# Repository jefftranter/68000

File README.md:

# 68000 single-board retro-computing project
Designs and code related to the Motorola 68000 microprocessor.

## Building the project hardware
1. [Order the board](TS2/v2.1/README.md)
2. Order the parts from the [bill of materials (BOM)](TS2/v2.1/bom.pdf)
3. Order the two FT232 USB -> serial breakout boards
4. Order the chip sockets:

| Layout    | Qty   | Width (inches)    | Notes                                 |
|:---       | ---:  | ---:              |:---                                   |
| DIP-8     | 1     | 0.3               | For the 555                           |
| DIP-14    | 17    | 0.3               | For a lot                             |
| DIP-16    | 8     | 0.3               | For even more                         |
| DIP-24    | 2     | 0.6               | Double width: for serial interface    |
| DIP-28    | 8     | 0.6               | Double width: for RAM & ROM           |
| DIP-64    | 1     | 0.9               | Triple width: for CPU.                |

The DIP-64 can be a little hard to obtain, you could cut DIP-40 sockets to same effect. However, it's inadvisable to 
directly solder the CPU directly to the board. If the heat damages the chip, there's 64 pins to de-solder.

5. Solder in the sockets. Applying some soldering flux can be of great help: the IC soldering pads are tiny, mainly to 
save space on the board.
6. Solder in the rest of the components
7. [Flash the ROM chips](http://jefftranter.blogspot.com/2016/12/building-68000-single-board-computer_7.html)
8. Fit all ICs into their sockets
9. Connect power (preferably through a lab bench power supply)
10. Connect a PC to the board through USB
11. Watch it boot
12. Have some retro-computing fun!

Copyright (c) 2016-2023 by Jeff Tranter <tranter@pobox.com>

The hardware design is Open Source Hardware, licensed under the The TAPR
Open Hardware License. You are welcome to build the circuit and use my
PCB layout.
See https://web.tapr.org/OHL/TAPR_Open_Hardware_License_v1.0.txt

Some code here is entirely written by me and others are ports of
existing software. Software written by me is released under the
following license:

Licensed under the Apache License, Version 2.0 (the "License");
you may not use this file except in compliance with the License.
You may obtain a copy of the License at

  http://www.apache.org/licenses/LICENSE-2.0

Unless required by applicable law or agreed to in writing, software
distributed under the License is distributed on an "AS IS" BASIS,
WITHOUT WARRANTIES OR CONDITIONS OF ANY KIND, either express or implied.
See the License for the specific language governing permissions and
limitations under the License.

Documentation written by me is licensed under a Creative Commons
Attribution 4.0 International License.
See https://creativecommons.org/licenses/by/4.0/

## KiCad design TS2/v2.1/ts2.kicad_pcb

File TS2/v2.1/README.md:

# TS2 PCB project

This is a Kicad project for the Teesside TS2 single board computer
from the book "Microprocessor Systems Design - 68000 Hardware,
Software, and Interfacing", third edition, by Alan Clements.

This is a modified version that simplifies the design by removing
circuitry that is not needed for operation as a single board computer.
Specifically, removed was:

- backplane interface and associated buffering.

- interrupt priority encoding and acknowledge circuitry.

- line drivers and receivers for serial ports (FTDI USB to serial
  adaptors are used instead) and support for host/terminal transparent
  mode. This also removes the need for +12V/-12V power supplies.

This is version 2.1 that makes the following additional changes:

- The hard to obtain 25LS2548 chip is replaced by more commonly
  available parts.

- The hard to obtain MC14411 baud rate generator is replaced by a
  smaller, simpler circuit using the more easily obtained 74HC4060.

See more details on my blog at http://jefftranter.blogspot.ca/

## PCB printing
For your convenience, a [v2.1-gerbers.zip](v2.1-gerbers.zip) zip file is included here that you can directly feed to a printing facility. It includes the gerber files for the copper tracings, soldermasks, silk screens, drill file and other printing requirements. 

The individual gerber files are included (duplicated) as well in this directory for direct inspection in KiCad. Don't forget to update the files in the zip if you export using different settings.

The files were generated with KiCad v5.1.4 using the following settings. Note that your PCB manufacturer may require other settings. Check their site for the proper gerber and drill file export settings - don't use a printing facility that doesn't specify how to export the files!

### Gerber export settings

### Drill file export

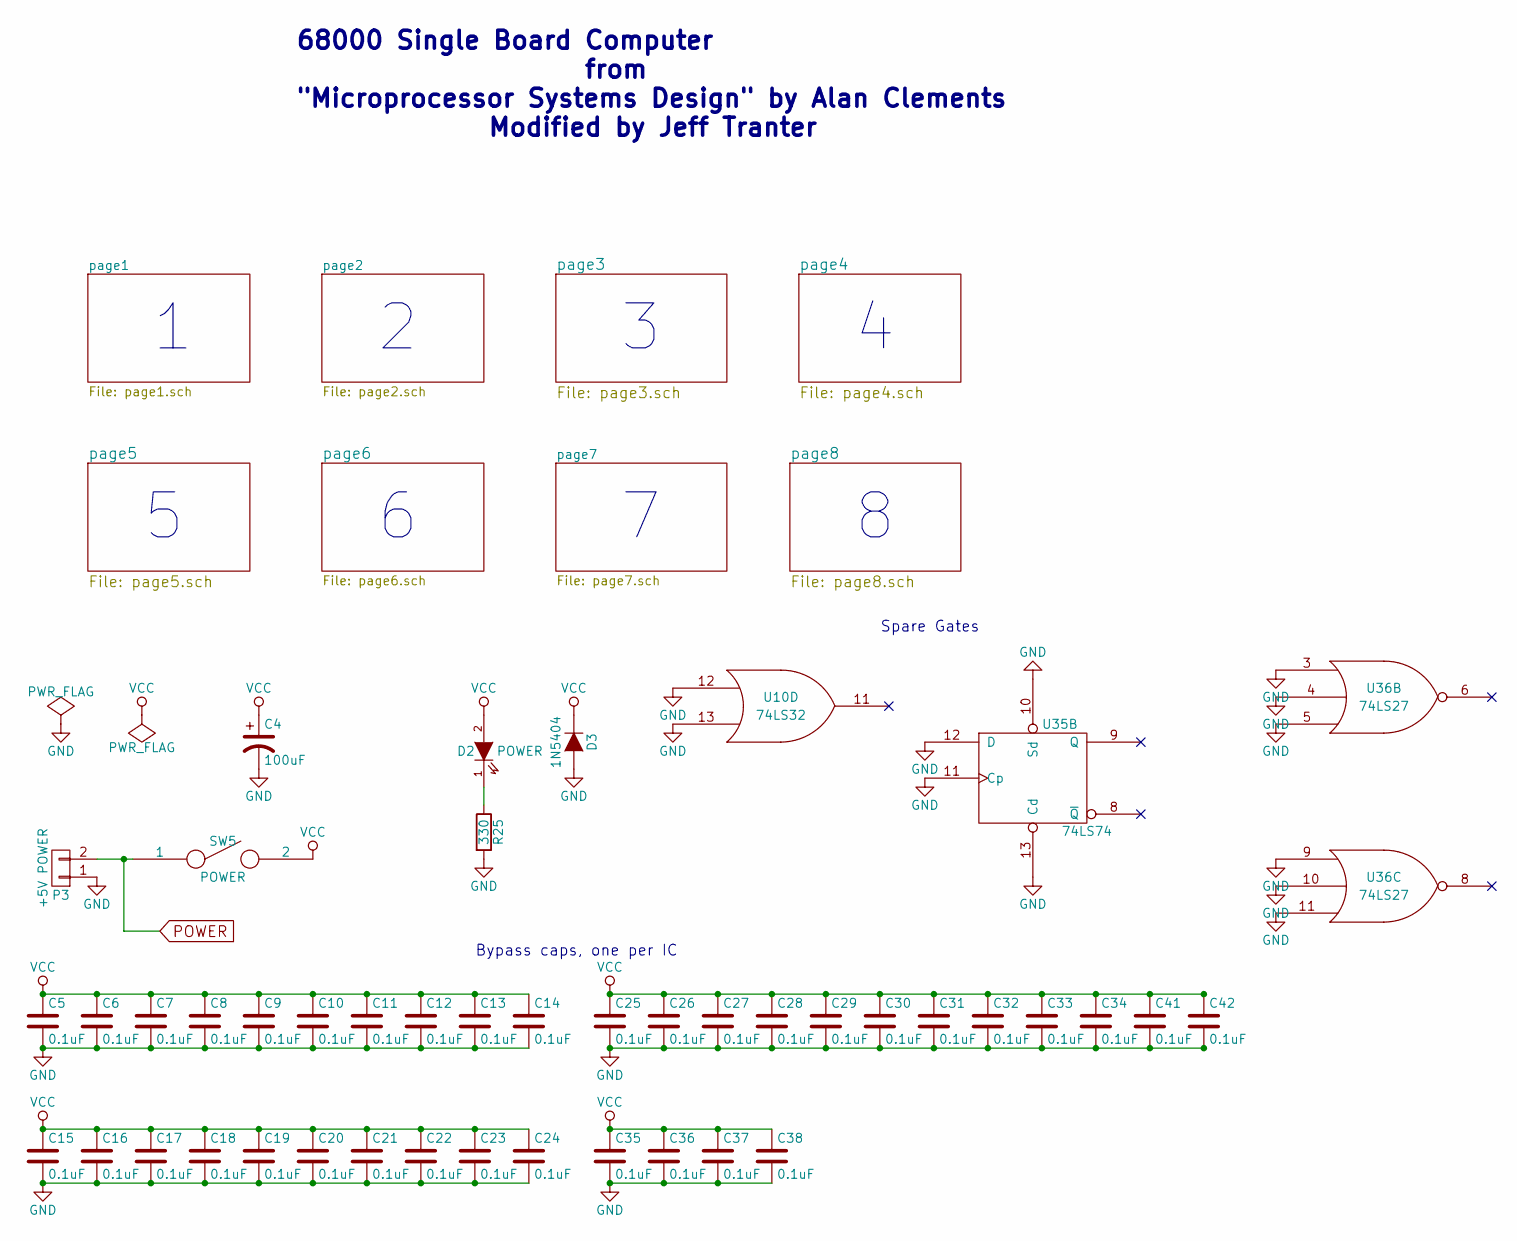
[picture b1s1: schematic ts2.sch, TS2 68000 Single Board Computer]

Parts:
C4: 100uF; C_Radial_D5_L6_P2.5
C5, C6, C7, C8, C9, C10, C11, C12, C13, C14, C15, C16, C17, C18, C19, C20, C21, C22, C23, C24, C25, C26, C27, C28, C29, C30, C31, C32, C33, C34, C35, C36, C37, C38, C41, C42: 0.1uF; C_Disc_D3_P2.5
D2: POWER; PINHEAD1-2
D3: 1N5404; Diode_DO-35_SOD27_Horizontal_RM10
P3: +5V POWER; PINHEAD1-2
R25: 330; Resistor_Horizontal_RM7mm
SW5: POWER; PINHEAD1-3
U10: 74LS32; DIP-14_W7.62mm
U35: 74LS74; DIP-14_W7.62mm
U36: 74LS27; DIP-14_W7.62mm

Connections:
GND: C4.2, C5.2, C6.2, C7.2, C8.2, C9.2, C10.2, C11.2, C12.2, C13.2, C14.2, C15.2, C16.2, C17.2, C18.2, C19.2, C20.2, C21.2, C22.2, C23.2, C24.2, C25.2, C26.2, C27.2, C28.2, C29.2, C30.2, C31.2, C32.2, C33.2, C34.2, C35.2, C36.2, C37.2, C38.2, C41.2, C42.2, D3.2 (A), P3.1, R25.2, U10.7 (GND), U10.12, U10.13, U35.7 (GND), U35.10 (Sd), U35.11 (Cp), U35.12 (D), U35.13 (Cd), U36.3, U36.4, U36.5, U36.7 (GND), U36.9, U36.10, U36.11; also elsewhere on the board
unnamed: D2.1 (K), R25.1
POWER: P3.2, SW5.1; also elsewhere on the board

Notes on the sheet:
68000 Single Board Computer from "Microprocessor Systems Design" by Alan Clements Modified by Jeff Tranter
Bypass caps, one per IC
Spare Gates

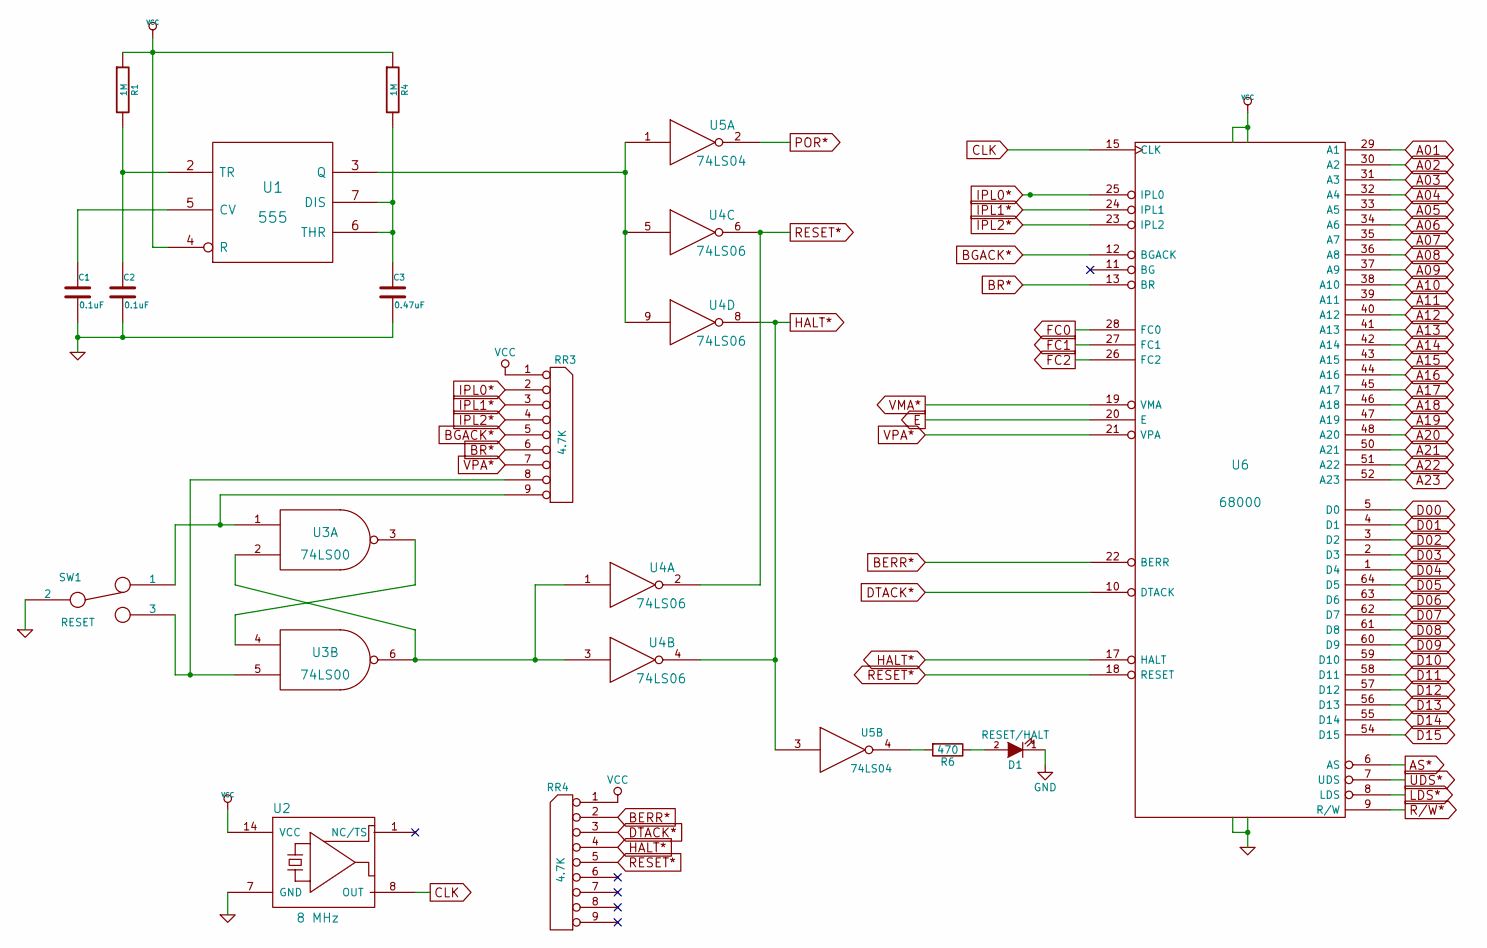
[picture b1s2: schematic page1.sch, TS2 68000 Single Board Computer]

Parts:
C1, C2: 0.1uF; C_Disc_D3_P2.5
C3: 0.47uF; C_Disc_D12_P7.75
D1: RESET/HALT; PINHEAD1-2
R1, R4: 1M; Resistor_Horizontal_RM7mm
R6: 470; Resistor_Horizontal_RM7mm
RR3, RR4: 4.7K; Resistor_Array_SIP8
SW1: RESET; PINHEAD1-3
U1: 555; DIP-8_W7.62mm
U2: 8 MHz; DIP-14_W7.62mm
U3: 74LS00; DIP-14_W7.62mm
U4: 74LS06; DIP-14_W7.62mm
U5: 74LS04; DIP-14_W7.62mm
U6: 68000; DIP-64_W22.86mm

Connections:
A01: U6.29 (A1); also elsewhere on the board
A02: U6.30 (A2); also elsewhere on the board
A03: U6.31 (A3); also elsewhere on the board
A04: U6.32 (A4); also elsewhere on the board
A05: U6.33 (A5); also elsewhere on the board
A06: U6.34 (A6); also elsewhere on the board
A07: U6.35 (A7); also elsewhere on the board
A08: U6.36 (A8); also elsewhere on the board
A09: U6.37 (A9); also elsewhere on the board
A10: U6.38 (A10); also elsewhere on the board
A11: U6.39 (A11); also elsewhere on the board
A12: U6.40 (A12); also elsewhere on the board
A13: U6.41 (A13); also elsewhere on the board
A14: U6.42 (A14); also elsewhere on the board
A15: U6.43 (A15); also elsewhere on the board
A16: U6.44 (A16); also elsewhere on the board
A17: U6.45 (A17); also elsewhere on the board
A18: U6.46 (A18); also elsewhere on the board
A19: U6.47 (A19); also elsewhere on the board
A20: U6.48 (A20); also elsewhere on the board
A21: U6.50 (A21); also elsewhere on the board
A22: U6.51 (A22); also elsewhere on the board
A23: U6.52 (A23); also elsewhere on the board
BERR*: RR4.2, U6.22 (BERR); also elsewhere on the board
BGACK*: RR3.5, U6.12 (BGACK)
BR*: RR3.6, U6.13 (BR)
CLK: U2.8 (OUT), U6.15 (CLK); also elsewhere on the board
D00: U6.5 (D0); also elsewhere on the board
D01: U6.4 (D1); also elsewhere on the board
D02: U6.3 (D2); also elsewhere on the board
D03: U6.2 (D3); also elsewhere on the board
D04: U6.1 (D4); also elsewhere on the board
D05: U6.64 (D5); also elsewhere on the board
D06: U6.63 (D6); also elsewhere on the board
D07: U6.62 (D7); also elsewhere on the board
D08: U6.61 (D8); also elsewhere on the board
D09: U6.60 (D9); also elsewhere on the board
D10: U6.59 (D10); also elsewhere on the board
D11: U6.58 (D11); also elsewhere on the board
D12: U6.57 (D12); also elsewhere on the board
D13: U6.56 (D13); also elsewhere on the board
D14: U6.55 (D14); also elsewhere on the board
D15: U6.54 (D15); also elsewhere on the board
DTACK*: RR4.3, U6.10 (DTACK); also elsewhere on the board
E: U6.20 (E); also elsewhere on the board
FC0: U6.28 (FC0); also elsewhere on the board
FC1: U6.27 (FC1); also elsewhere on the board
FC2: U6.26 (FC2); also elsewhere on the board
GND: C1.2, C2.2, C3.2, D1.1 (K), SW1.2, U1.1 (GND), U2.7 (GND), U3.7 (GND), U4.7 (GND), U5.7 (GND), U6.16 (GND), U6.53 (GND); also elsewhere on the board
HALT*: RR4.4, U4.4, U4.8, U5.3, U6.17 (HALT)
IPL0*: RR3.2, U6.25 (IPL0); also elsewhere on the board
IPL1*: RR3.3, U6.24 (IPL1); also elsewhere on the board
IPL2*: RR3.4, U6.23 (IPL2); also elsewhere on the board
LDS*: U6.8 (LDS); also elsewhere on the board
unnamed: C1.1, U1.5 (CV)
unnamed: C2.1, R1.2, U1.2 (TR)
unnamed: C3.1, R4.2, U1.6 (THR), U1.7 (DIS)
unnamed: D1.2 (A), R6.1
unnamed: R6.2, U5.4
unnamed: RR3.8, SW1.3, U3.5
unnamed: RR3.9, SW1.1, U3.1
unnamed: U1.3 (Q), U4.5, U4.9, U5.1
unnamed: U3.2, U3.6, U4.1, U4.3
unnamed: U3.3, U3.4
POR*: U5.2; also elsewhere on the board
R/W*: U6.9 (R/W); also elsewhere on the board
RESET*: RR4.5, U4.2, U4.6, U6.18 (RESET)
UDS*: U6.7 (UDS); also elsewhere on the board
VMA*: U6.19 (VMA); also elsewhere on the board
VPA*: RR3.7, U6.21 (VPA); also elsewhere on the board

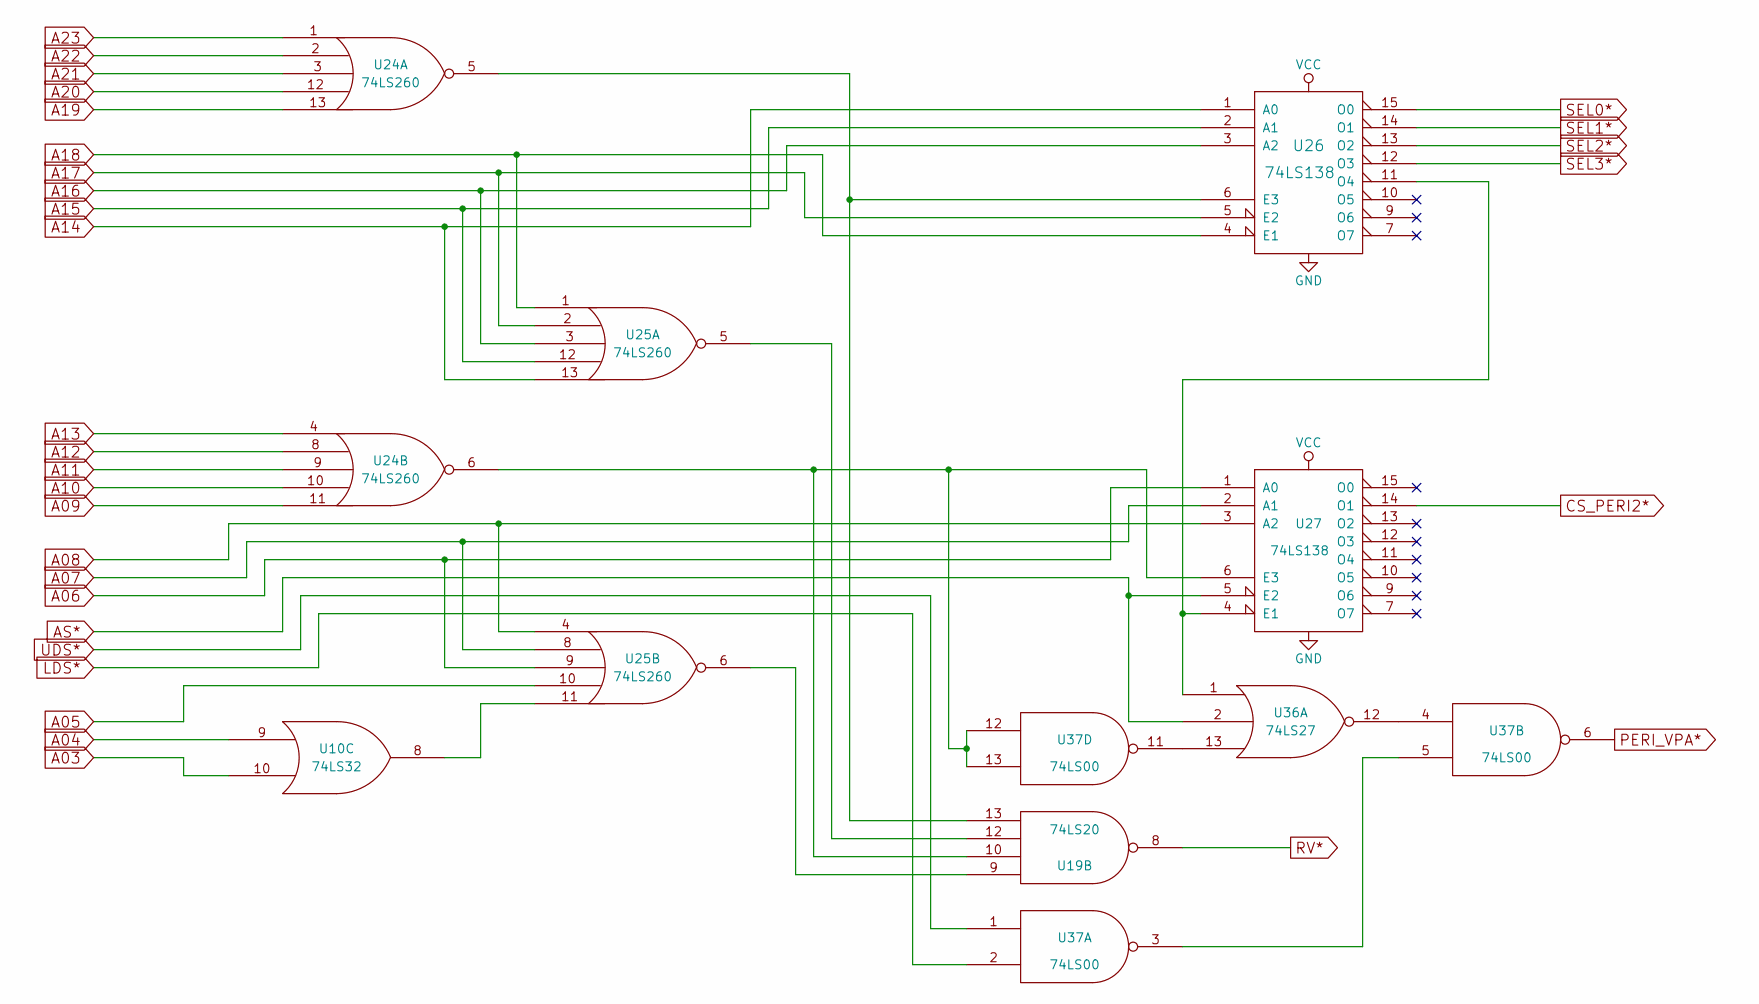
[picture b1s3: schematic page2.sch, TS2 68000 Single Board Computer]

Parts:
U10: 74LS32; DIP-14_W7.62mm
U19: 74LS20; DIP-14_W7.62mm
U24, U25: 74LS260; DIP-14_W7.62mm
U26, U27: 74LS138; DIP-16_W7.62mm
U36: 74LS27; DIP-14_W7.62mm
U37: 74LS00; DIP-14_W7.62mm

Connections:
A03: U10.10; also elsewhere on the board
A04: U10.9; also elsewhere on the board
A05: U25.10; also elsewhere on the board
A06: U25.9, U27.1 (A0); also elsewhere on the board
A07: U25.8, U27.2 (A1); also elsewhere on the board
A08: U25.4, U27.3 (A2); also elsewhere on the board
A09: U24.11; also elsewhere on the board
A10: U24.10; also elsewhere on the board
A11: U24.9; also elsewhere on the board
A12: U24.8; also elsewhere on the board
A13: U24.4; also elsewhere on the board
A14: U25.13, U26.1 (A0); also elsewhere on the board
A15: U25.12, U26.2 (A1); also elsewhere on the board
A16: U25.3, U26.3 (A2); also elsewhere on the board
A17: U25.2, U26.5 (E2); also elsewhere on the board
A18: U25.1, U26.4 (E1); also elsewhere on the board
A19: U24.13; also elsewhere on the board
A20: U24.12; also elsewhere on the board
A21: U24.3; also elsewhere on the board
A22: U24.2; also elsewhere on the board
A23: U24.1; also elsewhere on the board
CS_PERI2*: U27.14 (O1); also elsewhere on the board
GND: U10.7 (GND), U19.7 (GND), U24.7 (GND), U25.7 (GND), U26.8 (GND), U27.8 (GND), U36.7 (GND), U37.7 (GND); also elsewhere on the board
LDS*: U37.2; also elsewhere on the board
unnamed: U10.8, U25.11
unnamed: U19.9, U25.6
unnamed: U19.10, U24.6, U27.6 (E3), U37.12, U37.13
unnamed: U19.12, U25.5
unnamed: U19.13, U24.5, U26.6 (E3)
unnamed: U26.11 (O4), U27.4 (E1), U36.1
unnamed: U36.12, U37.4
unnamed: U36.13, U37.11
unnamed: U37.3, U37.5
PERI_VPA*: U37.6; also elsewhere on the board
RV*: U19.8; also elsewhere on the board
SEL0*: U26.15 (O0); also elsewhere on the board
SEL1*: U26.14 (O1); also elsewhere on the board
SEL2*: U26.13 (O2); also elsewhere on the board
SEL3*: U26.12 (O3); also elsewhere on the board
UDS*: U37.1; also elsewhere on the board

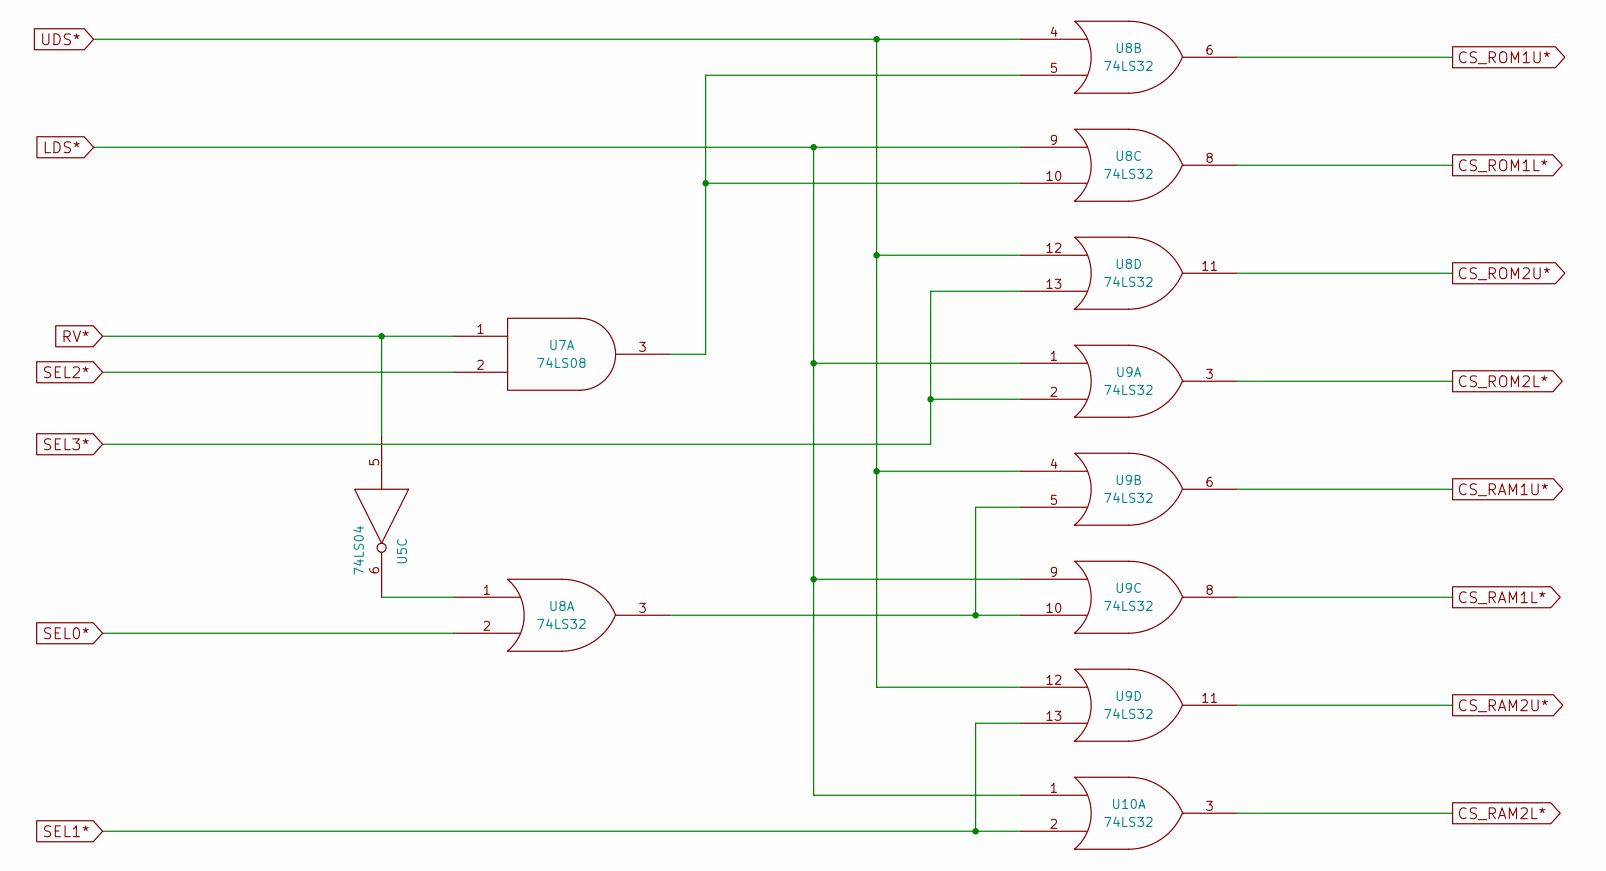
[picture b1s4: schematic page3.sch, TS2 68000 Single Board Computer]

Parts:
U5: 74LS04; DIP-14_W7.62mm
U7: 74LS08; DIP-14_W7.62mm
U8, U9, U10: 74LS32; DIP-14_W7.62mm

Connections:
CS_RAM1L*: U9.8; also elsewhere on the board
CS_RAM1U*: U9.6; also elsewhere on the board
CS_RAM2L*: U10.3; also elsewhere on the board
CS_RAM2U*: U9.11; also elsewhere on the board
CS_ROM1L*: U8.8; also elsewhere on the board
CS_ROM1U*: U8.6; also elsewhere on the board
CS_ROM2L*: U9.3; also elsewhere on the board
CS_ROM2U*: U8.11; also elsewhere on the board
GND: U5.7 (GND), U7.7 (GND), U8.7 (GND), U9.7 (GND), U10.7 (GND); also elsewhere on the board
LDS*: U8.9, U9.1, U9.9, U10.1; also elsewhere on the board
unnamed: U5.6, U8.1
unnamed: U7.3, U8.5, U8.10
unnamed: U8.3, U9.5, U9.10
RV*: U5.5, U7.1; also elsewhere on the board
SEL0*: U8.2; also elsewhere on the board
SEL1*: U9.13, U10.2; also elsewhere on the board
SEL2*: U7.2; also elsewhere on the board
SEL3*: U8.13, U9.2; also elsewhere on the board
UDS*: U8.4, U8.12, U9.4, U9.12; also elsewhere on the board

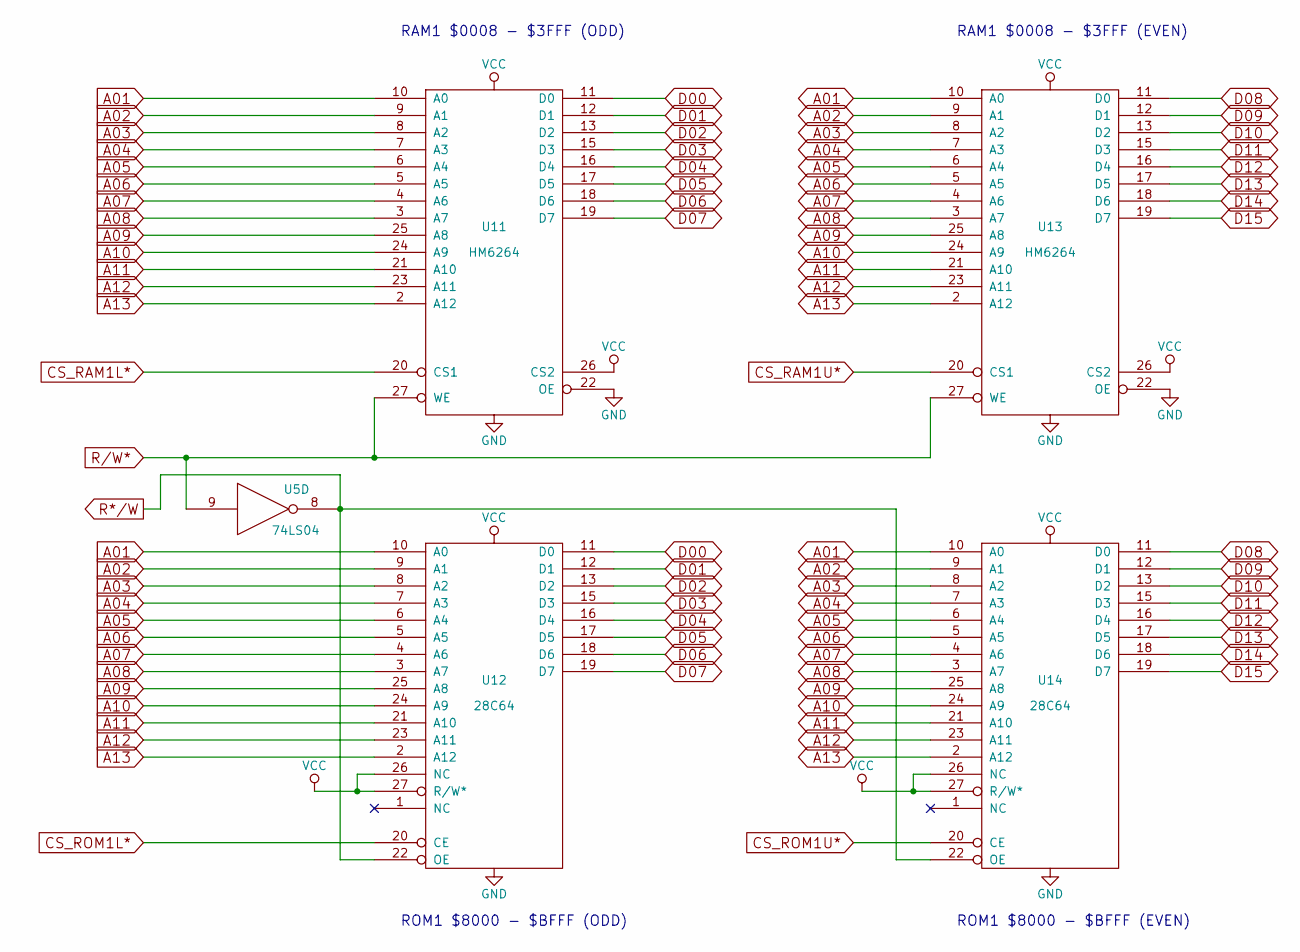
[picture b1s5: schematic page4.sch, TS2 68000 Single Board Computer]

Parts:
U5: 74LS04; DIP-14_W7.62mm
U11, U13: HM6264; DIP-28_W15.24mm
U12, U14: 28C64; DIP-28_W15.24mm

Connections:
A01: U11.10 (A0), U12.10 (A0), U13.10 (A0), U14.10 (A0); also elsewhere on the board
A02: U11.9 (A1), U12.9 (A1), U13.9 (A1), U14.9 (A1); also elsewhere on the board
A03: U11.8 (A2), U12.8 (A2), U13.8 (A2), U14.8 (A2); also elsewhere on the board
A04: U11.7 (A3), U12.7 (A3), U13.7 (A3), U14.7 (A3); also elsewhere on the board
A05: U11.6 (A4), U12.6 (A4), U13.6 (A4), U14.6 (A4); also elsewhere on the board
A06: U11.5 (A5), U12.5 (A5), U13.5 (A5), U14.5 (A5); also elsewhere on the board
A07: U11.4 (A6), U12.4 (A6), U13.4 (A6), U14.4 (A6); also elsewhere on the board
A08: U11.3 (A7), U12.3 (A7), U13.3 (A7), U14.3 (A7); also elsewhere on the board
A09: U11.25 (A8), U12.25 (A8), U13.25 (A8), U14.25 (A8); also elsewhere on the board
A10: U11.24 (A9), U12.24 (A9), U13.24 (A9), U14.24 (A9); also elsewhere on the board
A11: U11.21 (A10), U12.21 (A10), U13.21 (A10), U14.21 (A10); also elsewhere on the board
A12: U11.23 (A11), U12.23 (A11), U13.23 (A11), U14.23 (A11); also elsewhere on the board
A13: U11.2 (A12), U12.2 (A12), U13.2 (A12), U14.2 (A12); also elsewhere on the board
CS_RAM1L*: U11.20 (CS1); also elsewhere on the board
CS_RAM1U*: U13.20 (CS1); also elsewhere on the board
CS_ROM1L*: U12.20 (CE); also elsewhere on the board
CS_ROM1U*: U14.20 (CE); also elsewhere on the board
D00: U11.11 (D0), U12.11 (D0); also elsewhere on the board
D01: U11.12 (D1), U12.12 (D1); also elsewhere on the board
D02: U11.13 (D2), U12.13 (D2); also elsewhere on the board
D03: U11.15 (D3), U12.15 (D3); also elsewhere on the board
D04: U11.16 (D4), U12.16 (D4); also elsewhere on the board
D05: U11.17 (D5), U12.17 (D5); also elsewhere on the board
D06: U11.18 (D6), U12.18 (D6); also elsewhere on the board
D07: U11.19 (D7), U12.19 (D7); also elsewhere on the board
D08: U13.11 (D0), U14.11 (D0); also elsewhere on the board
D09: U13.12 (D1), U14.12 (D1); also elsewhere on the board
D10: U13.13 (D2), U14.13 (D2); also elsewhere on the board
D11: U13.15 (D3), U14.15 (D3); also elsewhere on the board
D12: U13.16 (D4), U14.16 (D4); also elsewhere on the board
D13: U13.17 (D5), U14.17 (D5); also elsewhere on the board
D14: U13.18 (D6), U14.18 (D6); also elsewhere on the board
D15: U13.19 (D7), U14.19 (D7); also elsewhere on the board
GND: U5.7 (GND), U11.14 (GND), U11.22 (OE), U12.14 (GND), U13.14 (GND), U13.22 (OE), U14.14 (GND); also elsewhere on the board
R*/W: U5.8, U12.22 (OE), U14.22 (OE); also elsewhere on the board
R/W*: U5.9, U11.27 (WE), U13.27 (WE); also elsewhere on the board

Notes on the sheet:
RAM1 $0008 - $3FFF (ODD)
RAM1 $0008 - $3FFF (EVEN)
ROM1 $8000 - $BFFF (ODD)
ROM1 $8000 - $BFFF (EVEN)

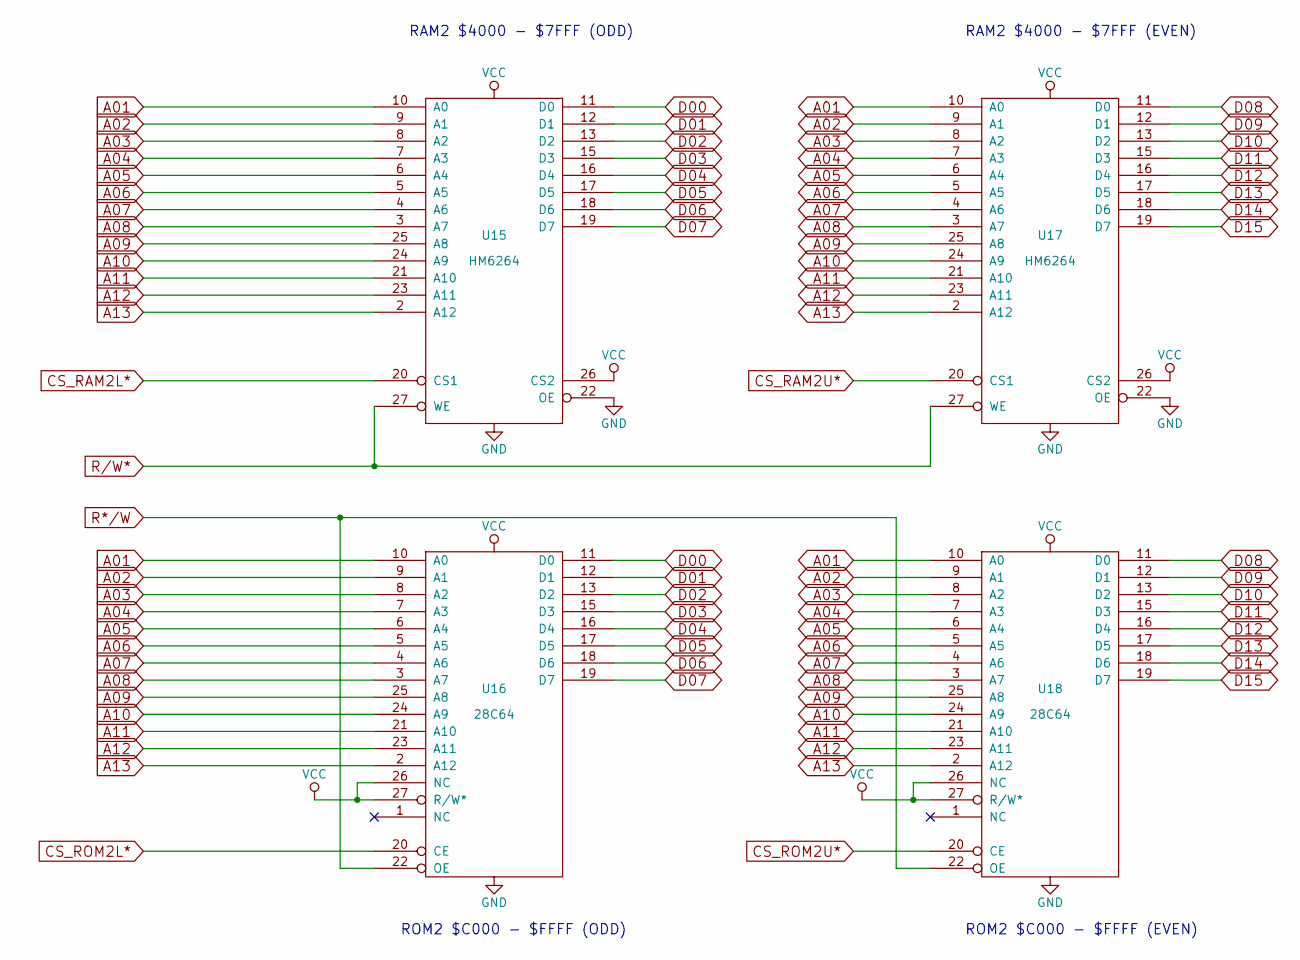
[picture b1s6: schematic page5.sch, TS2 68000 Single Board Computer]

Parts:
U15, U17: HM6264; DIP-28_W15.24mm
U16, U18: 28C64; DIP-28_W15.24mm

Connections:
A01: U15.10 (A0), U16.10 (A0), U17.10 (A0), U18.10 (A0); also elsewhere on the board
A02: U15.9 (A1), U16.9 (A1), U17.9 (A1), U18.9 (A1); also elsewhere on the board
A03: U15.8 (A2), U16.8 (A2), U17.8 (A2), U18.8 (A2); also elsewhere on the board
A04: U15.7 (A3), U16.7 (A3), U17.7 (A3), U18.7 (A3); also elsewhere on the board
A05: U15.6 (A4), U16.6 (A4), U17.6 (A4), U18.6 (A4); also elsewhere on the board
A06: U15.5 (A5), U16.5 (A5), U17.5 (A5), U18.5 (A5); also elsewhere on the board
A07: U15.4 (A6), U16.4 (A6), U17.4 (A6), U18.4 (A6); also elsewhere on the board
A08: U15.3 (A7), U16.3 (A7), U17.3 (A7), U18.3 (A7); also elsewhere on the board
A09: U15.25 (A8), U16.25 (A8), U17.25 (A8), U18.25 (A8); also elsewhere on the board
A10: U15.24 (A9), U16.24 (A9), U17.24 (A9), U18.24 (A9); also elsewhere on the board
A11: U15.21 (A10), U16.21 (A10), U17.21 (A10), U18.21 (A10); also elsewhere on the board
A12: U15.23 (A11), U16.23 (A11), U17.23 (A11), U18.23 (A11); also elsewhere on the board
A13: U15.2 (A12), U16.2 (A12), U17.2 (A12), U18.2 (A12); also elsewhere on the board
CS_RAM2L*: U15.20 (CS1); also elsewhere on the board
CS_RAM2U*: U17.20 (CS1); also elsewhere on the board
CS_ROM2L*: U16.20 (CE); also elsewhere on the board
CS_ROM2U*: U18.20 (CE); also elsewhere on the board
D00: U15.11 (D0), U16.11 (D0); also elsewhere on the board
D01: U15.12 (D1), U16.12 (D1); also elsewhere on the board
D02: U15.13 (D2), U16.13 (D2); also elsewhere on the board
D03: U15.15 (D3), U16.15 (D3); also elsewhere on the board
D04: U15.16 (D4), U16.16 (D4); also elsewhere on the board
D05: U15.17 (D5), U16.17 (D5); also elsewhere on the board
D06: U15.18 (D6), U16.18 (D6); also elsewhere on the board
D07: U15.19 (D7), U16.19 (D7); also elsewhere on the board
D08: U17.11 (D0), U18.11 (D0); also elsewhere on the board
D09: U17.12 (D1), U18.12 (D1); also elsewhere on the board
D10: U17.13 (D2), U18.13 (D2); also elsewhere on the board
D11: U17.15 (D3), U18.15 (D3); also elsewhere on the board
D12: U17.16 (D4), U18.16 (D4); also elsewhere on the board
D13: U17.17 (D5), U18.17 (D5); also elsewhere on the board
D14: U17.18 (D6), U18.18 (D6); also elsewhere on the board
D15: U17.19 (D7), U18.19 (D7); also elsewhere on the board
GND: U15.14 (GND), U15.22 (OE), U16.14 (GND), U17.14 (GND), U17.22 (OE), U18.14 (GND); also elsewhere on the board
R*/W: U16.22 (OE), U18.22 (OE); also elsewhere on the board
R/W*: U15.27 (WE), U17.27 (WE); also elsewhere on the board

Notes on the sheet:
RAM2 $4000 - $7FFF (ODD)
RAM2 $4000 - $7FFF (EVEN)
ROM2 $C000 - $FFFF (ODD)
ROM2 $C000 - $FFFF (EVEN)

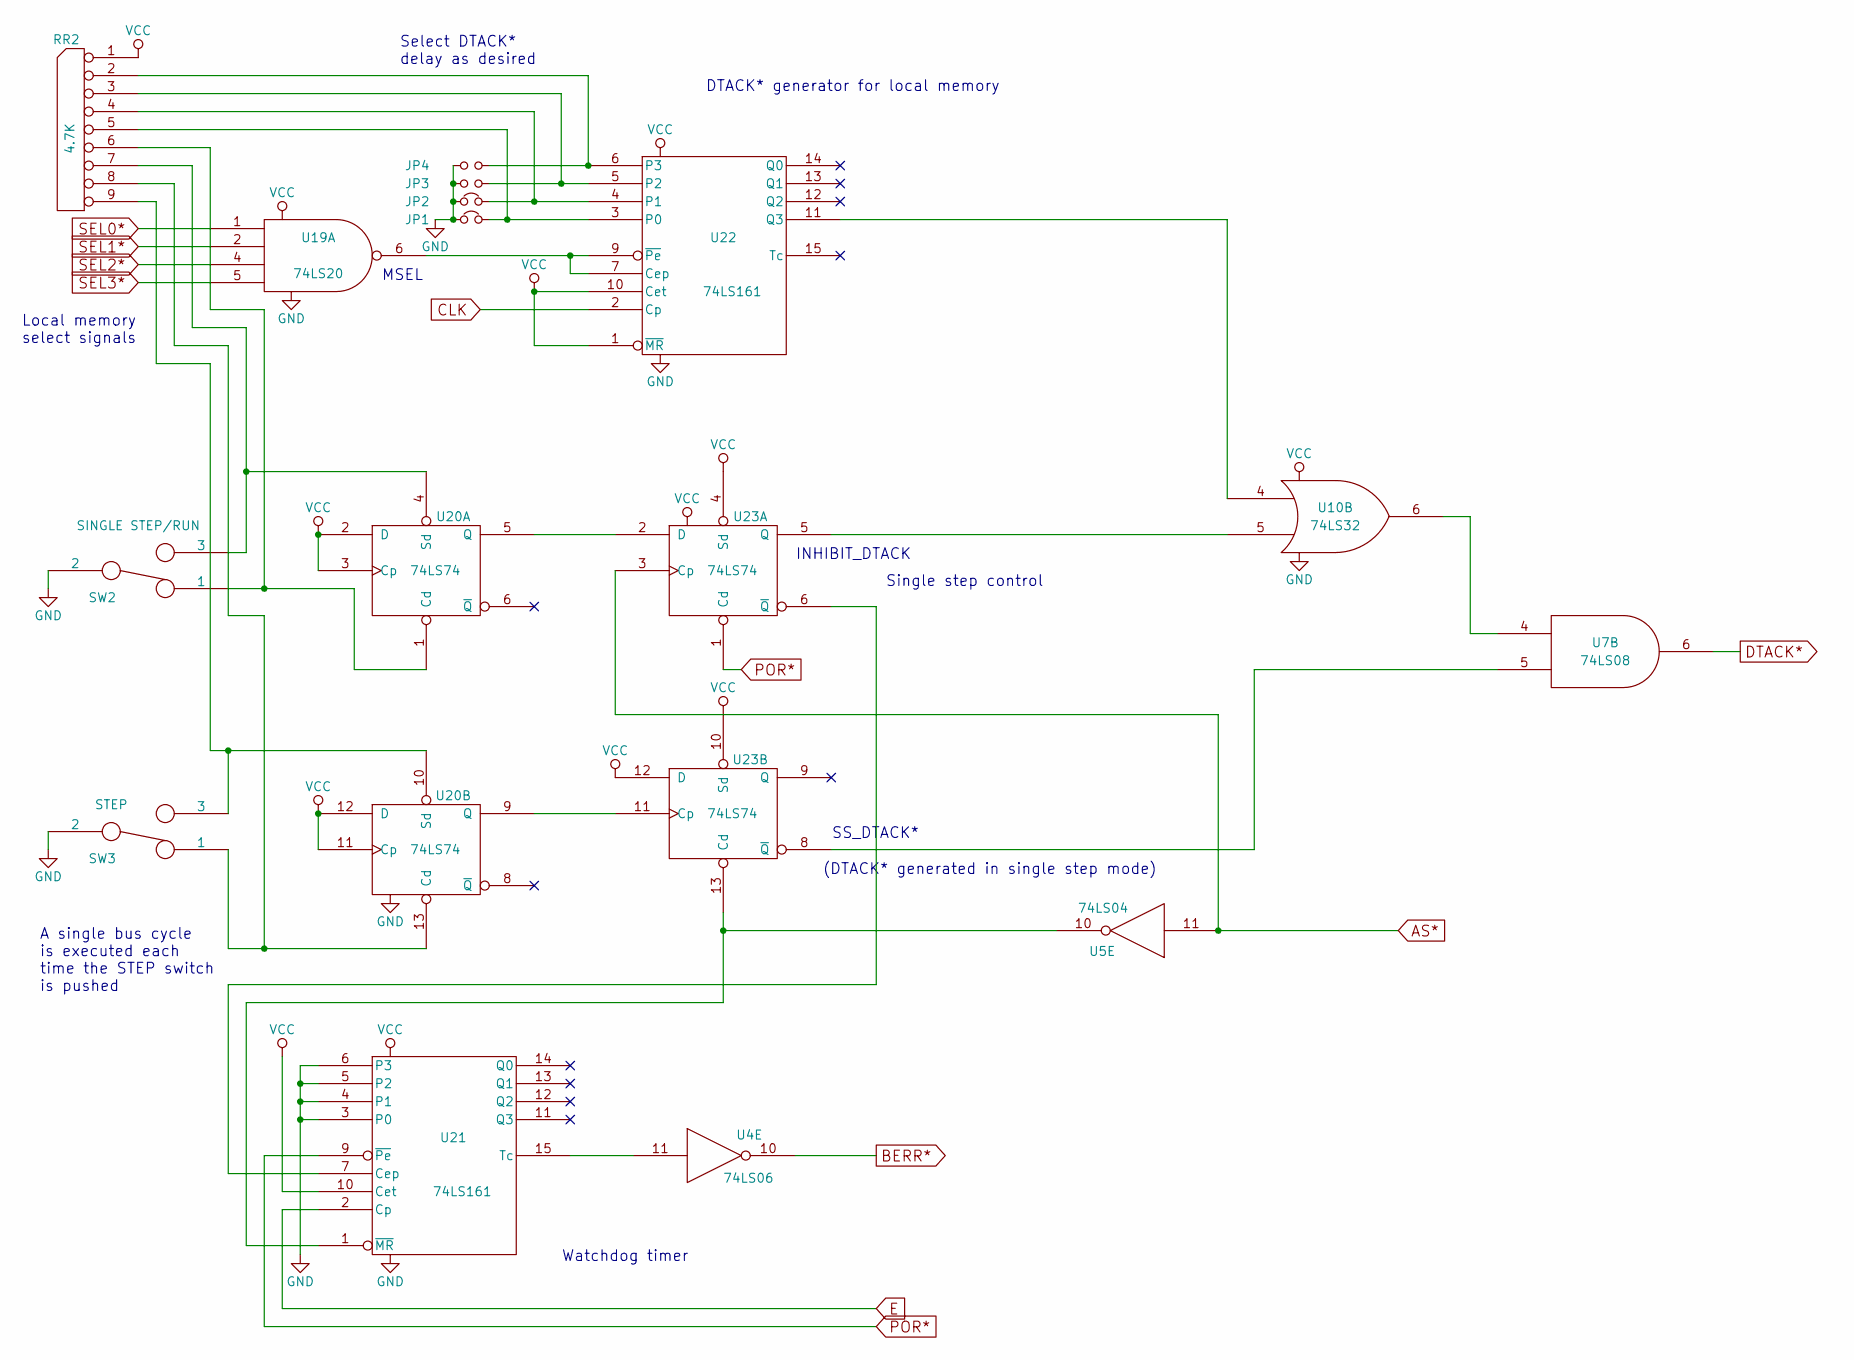
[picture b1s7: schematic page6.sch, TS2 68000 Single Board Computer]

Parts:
JP1, JP2: Jumper_NC_Small; PINHEAD1-2
JP3, JP4: Jumper_NO_Small; PINHEAD1-2
RR2: 4.7K; Resistor_Array_SIP8
SW2: SINGLE STEP/RUN; PINHEAD1-3
SW3: STEP; PINHEAD1-3
U4: 74LS06; DIP-14_W7.62mm
U5: 74LS04; DIP-14_W7.62mm
U7: 74LS08; DIP-14_W7.62mm
U10: 74LS32; DIP-14_W7.62mm
U19: 74LS20; DIP-14_W7.62mm
U20, U23: 74LS74; DIP-14_W7.62mm
U21, U22: 74LS161; DIP-16_W7.62mm

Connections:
BERR*: U4.10; also elsewhere on the board
CLK: U22.2 (Cp); also elsewhere on the board
DTACK*: U7.6; also elsewhere on the board
E: U21.2 (Cp); also elsewhere on the board
GND: JP1.1, JP2.1, JP3.1, JP4.1, SW2.2, SW3.2, U4.7 (GND), U5.7 (GND), U7.7 (GND), U10.7 (GND), U19.7 (GND), U20.7 (GND), U21.3 (P0), U21.4 (P1), U21.5 (P2), U21.6 (P3), U21.8 (GND), U22.8 (GND), U23.7 (GND); also elsewhere on the board
unnamed: JP1.2, RR2.5, U22.3 (P0)
unnamed: JP2.2, RR2.4, U22.4 (P1)
unnamed: JP3.2, RR2.3, U22.5 (P2)
unnamed: JP4.2, RR2.2, U22.6 (P3)
unnamed: RR2.6, SW2.1, U20.1 (Cd)
unnamed: RR2.7, SW2.3, U20.4 (Sd)
unnamed: RR2.8, SW3.1, U20.13 (Cd)
unnamed: RR2.9, SW3.3, U20.10 (Sd)
unnamed: U10.4, U22.11 (Q3)
unnamed: U10.5, U23.5 (Q)
unnamed: U7.4, U10.6
unnamed: U19.6, U22.7 (Cep), U22.9 (~Pe)
unnamed: U20.5 (Q), U23.2 (D)
unnamed: U20.9 (Q), U23.11 (Cp)
unnamed: U5.10, U21.1 (~MR), U23.13 (Cd)
unnamed: U21.7 (Cep), U23.6 (~Q)
unnamed: U4.11, U21.15 (Tc)
unnamed: U7.5, U23.8 (~Q)
POR*: U21.9 (~Pe), U23.1 (Cd); also elsewhere on the board
SEL0*: U19.1; also elsewhere on the board
SEL1*: U19.2; also elsewhere on the board
SEL2*: U19.4; also elsewhere on the board
SEL3*: U19.5; also elsewhere on the board

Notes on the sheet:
Select DTACK* delay as desired
Watchdog timer
(DTACK* generated in single step mode)
A single bus cycle is executed each time the STEP switch is pushed
Single step control
Local memory select signals
DTACK* generator for local memory
MSEL
INHIBIT_DTACK
SS_DTACK*

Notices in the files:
TS2/v2.1/ts2.kicad_pcb:
Copyright (c) 2017
